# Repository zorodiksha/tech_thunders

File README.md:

Practice ESP32 KiCAD for hackathon

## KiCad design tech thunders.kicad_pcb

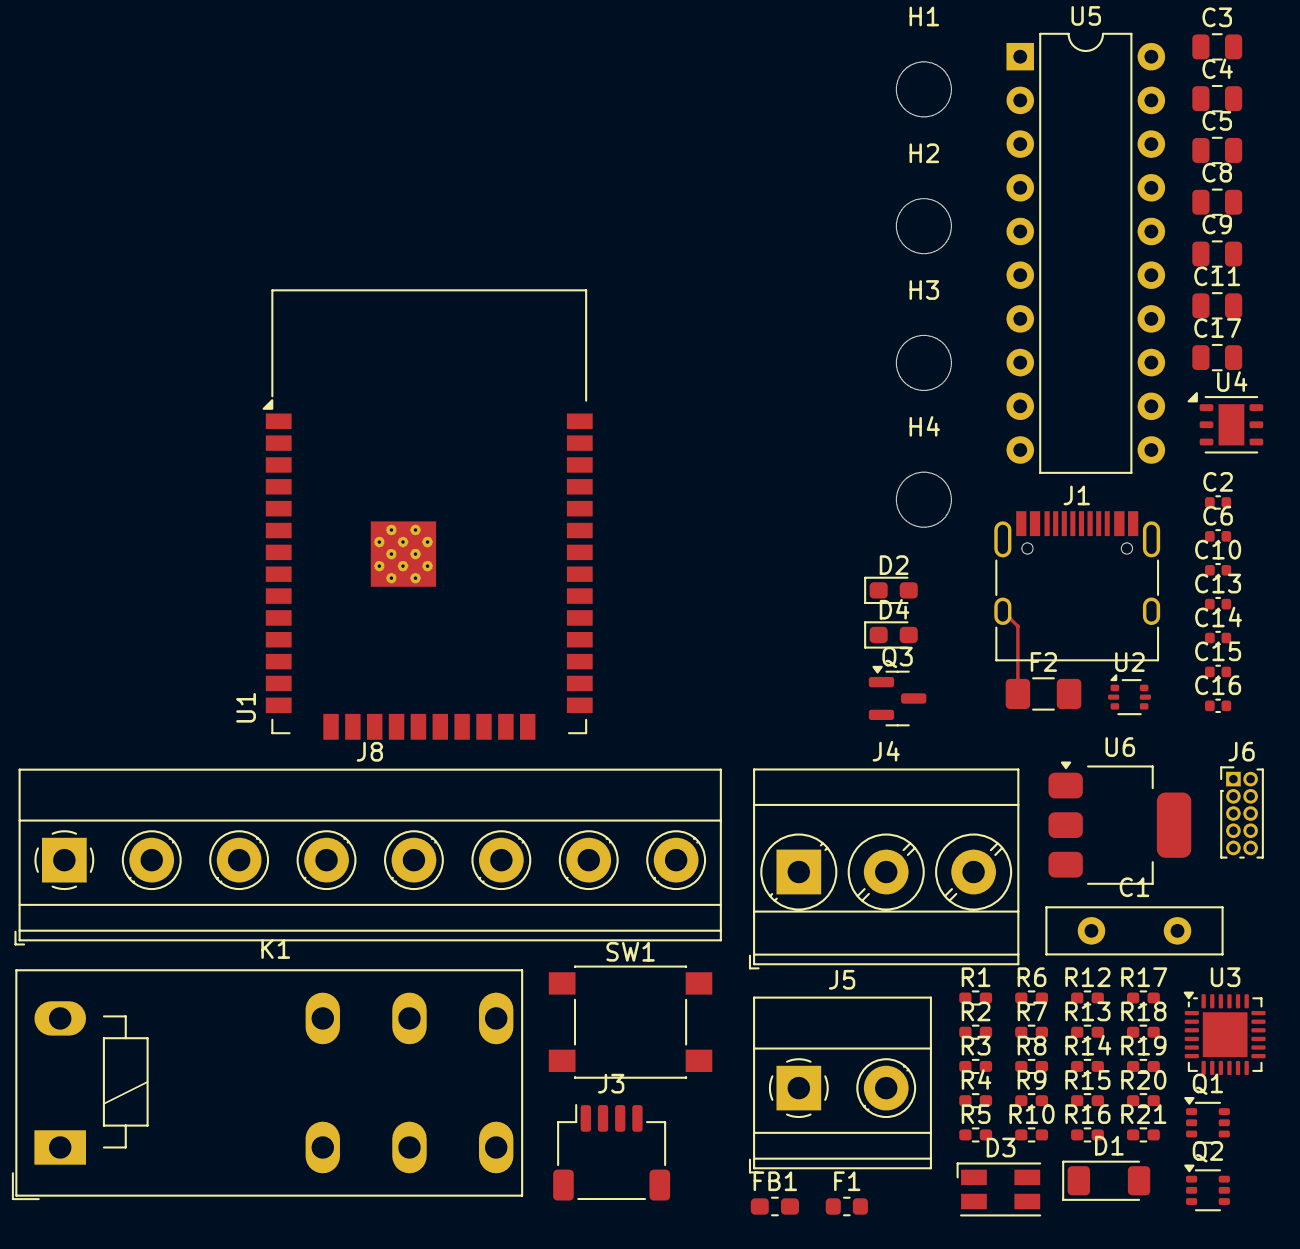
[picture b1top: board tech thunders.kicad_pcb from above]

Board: 2 copper layers, 63 parts (0 on the bottom side), 51 nets.

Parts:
C1: 1000U/25V; C_Disc_D10.0mm_W2.5mm_P5.00mm
C2, C6, C10, C13, C14, C15, C16: 100n; C_0402_1005Metric
C3: 47u; C_0805_2012Metric
C4, C5, C8, C9, C11, C17: 22u; C_0805_2012Metric
D1: LL4148; D_MiniMELF
D2: YELLOW; LED_0603_1608Metric_Pad1.05x0.95mm_HandSolder
D3: LED_RGBA; LED_RGB_Wuerth-PLCC4_3.2x2.8mm_150141M173100
D4: LED; LED_0603_1608Metric_Pad1.05x0.95mm_HandSolder
F1: Fuse; Fuse_0603_1608Metric
F2: Polyfuse_Small; Fuse_1206_3216Metric_Pad1.42x1.75mm_HandSolder
FB1: FerriteBead_Small; L_0603_1608Metric_Pad1.05x0.95mm_HandSolder
H1, H2, H3, H4: Hole_Pad; MountingHole_3.2mm_M3
J1: USB_C_Receptacle_USB2.0_16P; USB_C_Receptacle_HRO_TYPE-C-31-M-12
J3: Conn_01x04; JST_SH_SM04B-SRSS-TB_1x04-1MP_P1.00mm_Horizontal
J4: Screw_Terminal_01x03; TerminalBlock_Phoenix_MKDS-3-3-5.08_1x03_P5.08mm_Horizontal
J5: Screw_Terminal_01x08; TerminalBlock_Phoenix_MKDS-1,5-2-5.08_1x02_P5.08mm_Horizont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
J6: Conn_02x05_Odd_Even; PinHeader_2x05_P1.00mm_Vertical
J8: Screw_Terminal_01x02; TerminalBlock_Phoenix_MKDS-1,5-8-5.08_1x08_P5.08mm_Horizont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
K1: RT314A05; Relay_SPDT_Schrack-RT1-16A-FormC_RM5mm
Q1, Q2: UMH3N; SOT-363_SC-70-6
Q3: BC817; SOT-23
R1, R2: 51K; R_0402_1005Metric_Pad0.72x0.64mm_HandSolder
R3, R6, R7, R13, R14, R15: 10K; R_0402_1005Metric_Pad0.72x0.64mm_HandSolder
R4, R5, R18, R19, R20, R21: 22R; R_0402_1005Metric_Pad0.72x0.64mm_HandSolder
R8, R9, R10, R16, R17: 1K; R_0402_1005Metric_Pad0.72x0.64mm_HandSolder
R12: 47K; R_0402_1005Metric_Pad0.72x0.64mm_HandSolder
SW1: SW_SPST; SW_Push_1P1T_NO_6x6mm_H9.5mm
U1: ESP32-WROOM-32D
U2: USBLC6-2P6; SOT-666
U3: CP2104; QFN-24-1EP_4x4mm_P0.5mm_EP2.6x2.6mm
U4: Si7021-A20; DFN-6-1EP_3x3mm_P1mm_EP1.5x2.4mm
U5: 74AHCT245; DIP-20_W7.62mm
U6: TLYV1117LV; SOT-223-3_TabPin2

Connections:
+3.3V: C5.1, C6.1, C9.1, C11.1, C13.1, C16.1, C17.1, D3.4 (A), J3.2, J6.1, R3.1, R7.1, R12.1, R13.1, R14.1, U1.2 (VDD), U3.5 (VIO), U3.6 (VDD), U4.5 (VDD), U6.2 (VO)
+5V: C1.2, C2.1, C2.2, C3.1, C3.2, C4.1, C4.2, C5.2, C6.2, C8.1, C8.2, C9.2, C10.2, C11.2, C13.2, C14.2, C15.1, C15.2, C16.2, C17.2, D1.1 (K), D4.1 (K), F2.1, J1.A1 (GND), J1.A12 (GND), J1.B1 (GND), J1.B12 (GND), J1.S1 (SHIELD), J3.1, J6.9, J6.10, J8.2, K1.A1, Q3.2 (E), R1.2, R2.2, R6.1, R15.2, R17.1, SW1.1 (A), U1.1 (GND), U1.15 (GND), U1.38 (GND), U1.39 (GND), U2.2 (GND), U2.5 (VBUS), U3.2 (GND), U3.7 (REGIN), U3.8 (VBUS), U3.25 (GND), U4.2 (GND), U4.7 (PAD), U5.1 (A->B), U5.6 (A4), U5.7 (A5), U5.8 (A6), U5.9 (A7), U5.10 (GND), U5.19 (CE), U5.20 (VCC), U6.1 (GND), U6.3 (VI)
+5VP: FB1.1, J1.A4 (VBUS), J1.A9 (VBUS), J1.B4 (VBUS), J1.B9 (VBUS)
/DTR: Q1.4 (E2), Q2.2 (B1), U3.23 (~DTR)
/GPIO26: J6.3, U1.11 (IO26)
/GPIO27: J6.5, U1.12 (IO27)
/GPIO32: J6.7, U1.8 (IO32)
/GPIO33: J6.4, U1.9 (IO33)
/GPIO34: J6.6, U1.6 (IO34)
/GPIO35: J6.8, U1.7 (IO35)
/IO0: Q1.3 (C2), U1.25 (IO0)
/LEDSTR1: U1.27 (IO16), U5.2 (A0)
/LEDSTR2: U1.28 (IO17), U5.3 (A1)
/LEDSTR3: U1.30 (IO18), U5.4 (A2)
/LEDSTR4: U1.31 (IO19), U5.5 (A3)
/LED_B: R10.1, U1.13 (IO14)
/LED_G: R9.1, U1.23 (IO15)
/LED_R: R8.1, U1.16 (IO13)
/RELAY: R16.1, U1.10 (IO25)
/RTS: Q1.5 (B2), Q2.6 (C1), U3.19 (~RTS)
/RX: R4.2, U1.35 (TXD0/IO1)
/SW: C10.1, R7.2, SW1.2 (B), U1.33 (IO21)
unnamed: D1.2 (A), D2.1 (K), K1.A2, Q3.3 (C)
unnamed: D2.2 (A), R17.2
unnamed: D3.3 (BK), R10.2
unnamed: D3.2 (GK), R9.2
unnamed: D3.1 (RK), R8.2
unnamed: D4.2 (A), R6.2
unnamed: F2.2, FB1.2
unnamed: J1.A5 (CC1), R2.1
unnamed: J1.B5 (CC2), R1.1
unnamed: J1.A6 (D+), J1.B6 (D+), U2.4 (I/O2)
unnamed: J1.A7 (D-), J1.B7 (D-), U2.3 (I/O2)
unnamed: J3.3, R12.2, U4.1 (SDA)
unnamed: J3.4, R13.2, U4.6 (SCL)
unnamed: J4.1, K1.12
unnamed: J4.2, K1.11
unnamed: J4.3, K1.14
unnamed: F1.2, J5.1, J5.2
unnamed: C1.1, F1.1, J8.1
unnamed: Q3.1 (B), R15.1, R16.2
unnamed: C14.1, R14.2, U1.3 (EN)
unnamed: U2.6 (I/O1), U3.3 (D+)
unnamed: U2.1 (I/O1), U3.4 (D-)
unnamed: R5.1, U3.20 (RXD)
unnamed: R4.1, U3.21 (TXD)
unnamed: R3.2, U3.9 (~RST)
unnamed: R18.1, U5.18 (B0)
unnamed: R19.1, U5.17 (B1)
unnamed: R20.1, U5.16 (B2)
unnamed: R21.1, U5.15 (B3)
